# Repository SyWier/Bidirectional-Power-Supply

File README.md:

# Bidirectional-Power-Supply
Development of a bidirectional DC/DC power supply for battery applications.

The designed **developement** board is a **BUCK/BOOST converter**, based on the direction of the power flow. This enables us to charge a battery with voltage reduction or create an uninterrupted voltage output with voltage boost.

The developement board is easily configurable through serial communication, have test points for all the important signals and includes feedback LEDs.

## Directories
- Altium: **Altium** project of the hardware.
- CSS: **Code Composer Studio** project and other tools to flash the microcontroller

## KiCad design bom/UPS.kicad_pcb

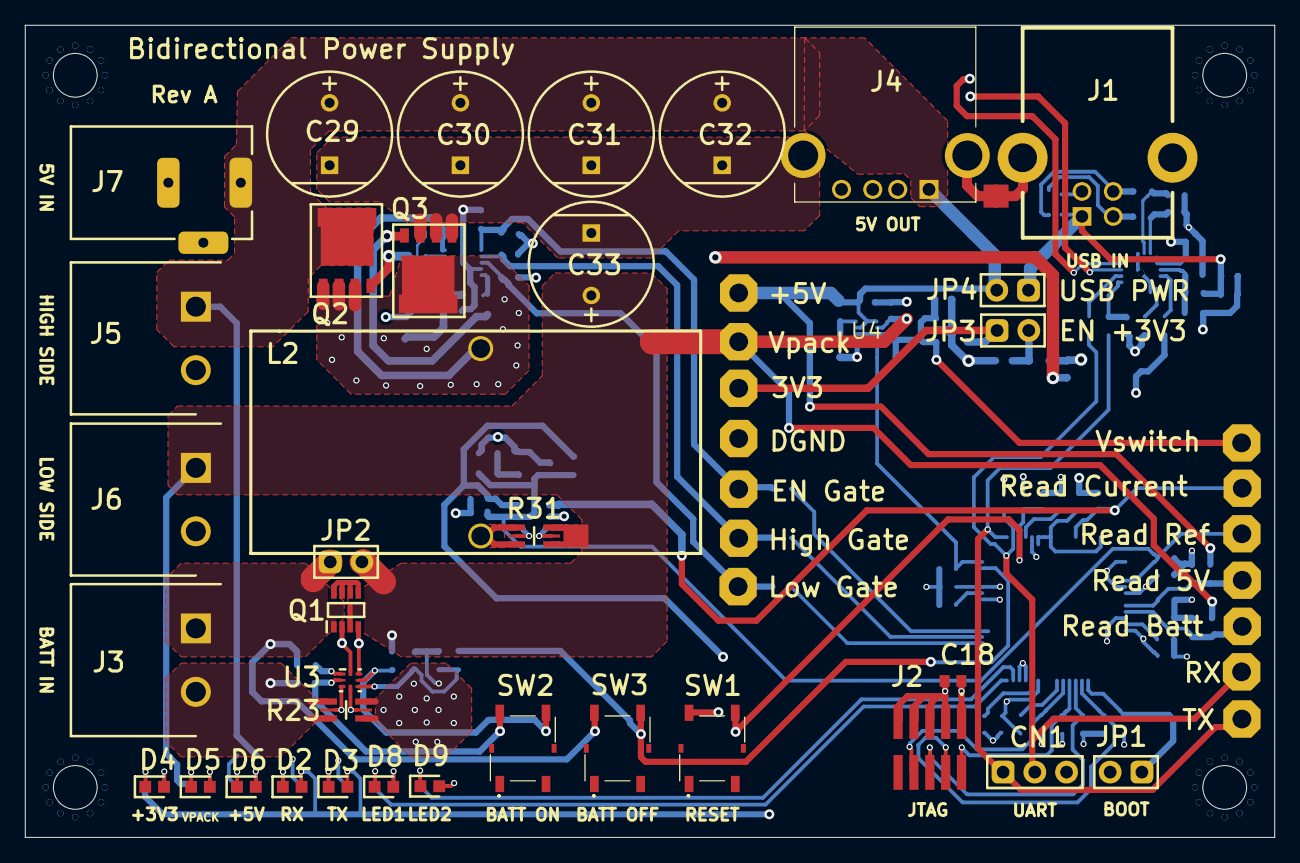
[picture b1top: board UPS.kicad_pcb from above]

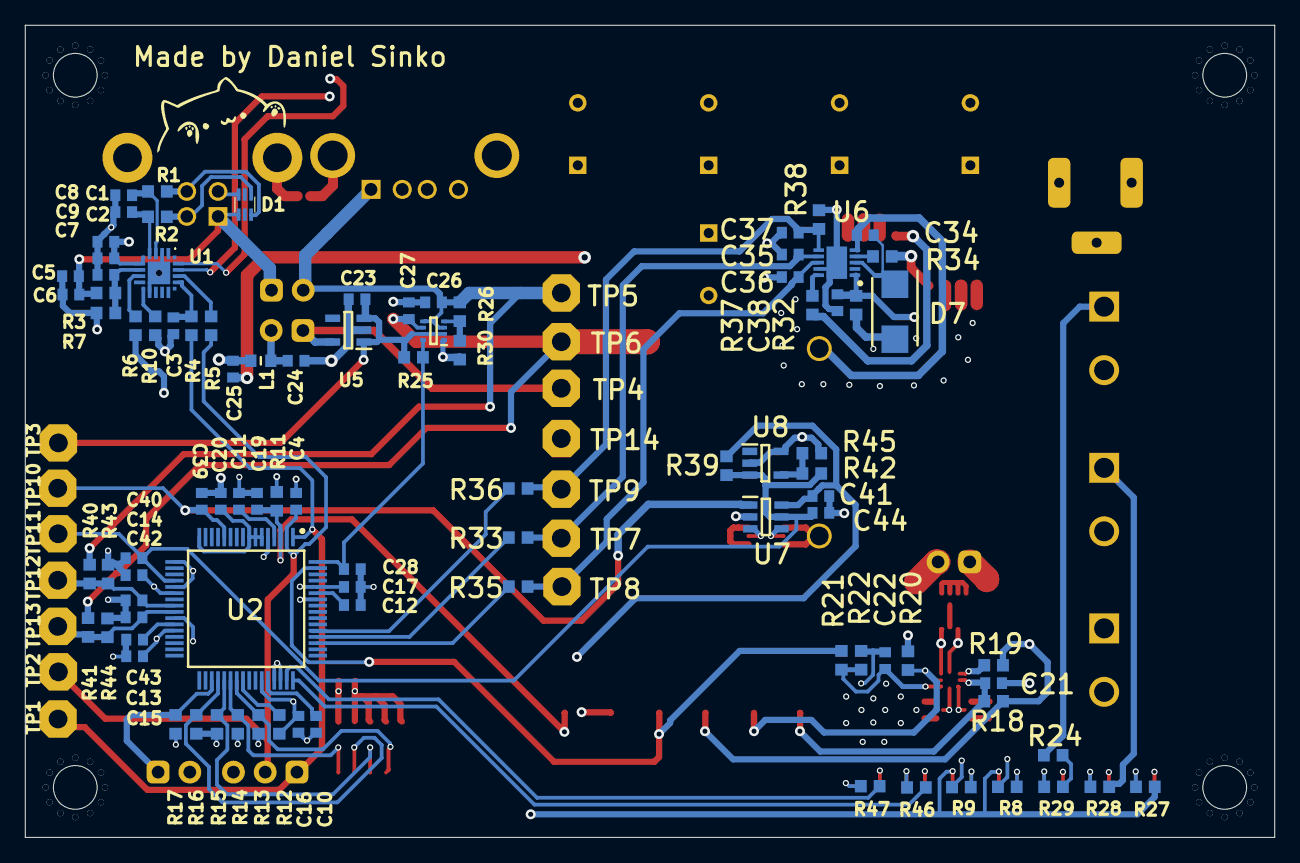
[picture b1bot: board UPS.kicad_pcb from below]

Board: 4 copper layers, 100.0 x 65.0 mm, 149 parts (108 on the bottom side), 78 nets.

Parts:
C1, C2, C35, C36, C37: 47pF; CAP0603
C3, C4: 470pF; CAP0603
C5, C8, C10, C11, C12, C13, C14, C20: 4.7uF; CAP0603
C6, C9, C15, C16, C17, C18, C19, C21, C22, C26, C27, C28, C41, C44: 100nF; CAP0603
C7, C23, C24, C34, C38, C39: 1uF; CAP0603
C25: 10uF; CAP0603
C29, C30, C31, C32: 1500uF; Aluminium Capacitor 10x12.5
C33: 470uF; Aluminium Capacitor 10x12.5
C40, C42, C43: 47nF; CAP0603
CN1: Pins 1x3; PIN-1X3
D1: ESDAULC6-3BP6; SOT-666
D2, D3, D4, D5, D6, D8, D9: Value; LED0603
D7: VS-MBRS130L-M3/5BT; SMB
H1, H2, H3, H4: Mounting_Hole_0; MOUNTING_HOLE_M3
J1: USB-B; USB-B-FEMALE
J2: FTSH-105-01-L-DV-K; CON-2x5-1.27
J3, J5, J6: 691313510002; WR-TBL-5.08/2-M
J4: USB-A; USB-A-FEMALE
J7: DC Power Jack; DC Power Jack Right Angled
JP1, JP2, JP3, JP4: Jumper; PIN-1X2
L1: Inductor; IND0603
L2: Inductor; COIL_HANDMADE
NT1, NT2, NT3: NetTie_1-1; NETTIE_1.85MM
Q1: ECH8695R-TL-W; SOT-28FL
Q2, Q3: N-MOSFET; SOT-669-5
R1, R2, R19: 20R; RES0603
R3: 22K1; RES0603
R4, R5, R18, R21, R33, R35, R36, R39: 100R; RES0603
R6, R20, R22: 1K; RES0603
R7: 47K5; RES0603
R8, R9, R24, R27, R28, R29, R46, R47: 330R; RES0603
R10, R25, R26, R30, R38, R45: 10K; RES0603
R11, R40, R41, R42: 3K3; RES0603
R12, R13, R14, R15, R16, R17, R43, R44: 4K7; RES0603
R23: 0R005; RES1206_KELVIN
R31: 0R010; RES1206_KELVIN
R32, R34, R37: 5R; RES0603
SW1, SW2, SW3: PTS526 Button; PTS526 SMG15J SMTR2 LFS
TP1, TP2, TP3, TP4, TP5, TP6, TP7, TP8, TP9, TP10, TP11, TP12, TP13, TP14: Test Point; TP-1.5HOLE
U1: CP2102N-A02-GQFN20R; QFN-20
U2: F280038PMRQ1; LQFP-64
U3: BQ2980; X2QFN-8
U4: TPS2116; SOTFL50P160X60-8N
U5: LP5907QMFX-3.3Q1; SOT23-5
U6: DGD05473FN-7; V-DFN3030-10
U7: INA181A1; SOT23-6
U8: TLV431; SOT23-5

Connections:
+1V2: C10.2, C11.2, C12.2, C13.2, U2.4, U2.27, U2.44, U2.59
+3V3: C8.2, C9.1, C15.2, C16.2, C17.2, C18.2, C24.2, C41.1, D2.2, D3.2, J2.1, JP3.2, L1.1, R6.1, R11.2, R12.2, R13.2, R14.2, R15.2, R16.2, R17.2, R27.2, R39.1, U1.6, U1.7, U2.28, U2.43, U2.60, U7.6
+3V3A: C14.2, C25.2, L1.2, U2.22
+5V: C26.2, C29.2, C30.2, C31.2, C32.2, C38.2, J4.1, J5.1, J7.1, JP4.2, Q2.3, R24.2, R26.2, R32.1, R40.2, TP5.1, U4.3, U4.5, U6.1
AGND: C14.1, C20.1, C25.1, C39.1, C40.1, C41.2, C42.1, C43.1, C44.2, NT2.2, R43.1, R44.1, R45.1, U2.17, U2.21, U7.2, U8.2, U8.5
BOOT0: R12.1, U2.40
BOOT1: JP1.1, R17.1, U2.35
D+: C1.2, R1.1, U1.4
D-: C2.2, R2.1, U1.5
DGND: C1.1, C2.1, C3.1, C4.1, C5.1, C6.2, C7.1, C8.1, C9.2, C10.1, C11.1, C12.1, C13.1, C15.1, C16.1, C17.1, C18.1, C19.2, C23.1, C24.1, C26.1, C27.1, C28.1, CN1.3, D1.6, D4.1, D8.1, D9.1, J1.0, J1.4, J2.3, J2.5, J2.7, J2.9, JP1.2, NT1.2, NT2.1, R7.1, R10.1, R30.1, SW1.1, TP14.1, U1.3, U1.12, U1.21, U2.5, U2.26, U2.45, U2.46, U2.58, U4.1, U5.2
Gate EN: R36.1, U2.53
Gate High: R33.1, U2.52
Gate Low: R35.1, U2.51
Gate_Common: C34.1, L2.1, Q2.2, Q3.3, U6.5
Gate_High: Q2.1, R34.2
Gate_Low: Q3.1, R37.2
NetC3_2: C3.2, R4.1, U1.17
NetC21_2: C21.2, R18.1, SW2.1, U3.2
NetC22_2: C22.2, R21.1, R22.2, U3.5
NetC34_2: C34.2, D7.1, U6.3
NetC35_2: C35.2, R33.2, TP7.1, U6.7
NetC36_2: C36.2, R35.2, TP8.1, U6.8
NetC37_2: C37.2, R36.2, R38.1, TP9.1, U6.6
NetD1_3: D1.3, J1.3, R1.2
NetD1_4: D1.4, J1.2, R2.2
NetD2_1: D2.1, R8.2
NetD3_1: D3.1, R9.2
NetD4_2: D4.2, R27.1
NetD5_2: D5.2, R28.1
NetD6_2: D6.2, R29.1
NetD7_2: D7.2, R32.2
NetD8_2: D8.2, R46.1
NetD9_2: D9.2, R47.1
NetJP3_1: JP3.1, TP4.1, U5.5
NetL2_2: L2.2, R31.1
NetNT3_1: NT3.1, R31.2
NetQ1_2: Q1.2, U3.8
NetQ1_4: Q1.4, U3.7
NetQ1_5: Q1.5, Q1.6, Q1.7, Q1.8
NetR5_1: R5.1, U1.18
NetR6_2: R6.2, U1.9
NetR8_1: R8.1, U1.20
NetR9_1: R9.1, U1.19
NetR10_2: R10.2, U1.11
NetR19_1: R19.1, U3.1
NetR20_1: R20.1, SW2.2, U3.6
NetR23_3: R23.3, U3.3
NetR23_4: R23.4, U3.4
NetR24_1: R24.1, R29.2
NetR26_1: R26.1, R30.2, U4.4
NetR34_1: R34.1, U6.4
NetR37_1: R37.1, U6.10
NetR42_1: R42.1, R45.2, U8.4
NetR46_2: R46.2, U2.48
NetR47_2: R47.2, U2.47
PGND: C22.1, C29.1, C30.1, C31.1, C32.1, C33.1, C35.1, C36.1, C37.1, C38.1, D5.1, D6.1, J4.4, J4.5, J5.2, J6.2, J7.2, J7.3, NT1.1, Q3.2, R22.1, R23.2, R38.2, U6.9, U6.11
Path Status: C28.2, R25.2, U2.64, U4.8
Read 5V: C42.2, R40.1, R43.2, TP12.1, U2.24
Read Battery: C43.2, R41.1, R44.2, TP13.1, U2.25
Read Current: C39.2, TP10.1, U2.12, U7.1
Read Ref: C40.2, C44.1, R39.2, R42.2, TP11.1, U2.20, U7.5, U8.3
SERIAL_RX: C4.2, CN1.2, R5.2, TP2.1, U2.2
SERIAL_TX: CN1.1, R4.2, TP1.1, U2.1
System Reset: R21.2, SW3.2, U2.63
TCK: J2.4, R16.1, U2.36
TDI: J2.8, R13.1, U2.39
TDO: J2.6, R15.1, U2.37
TMS: J2.2, R14.1, U2.38
VREFHI: C20.2, U2.6, U2.7, U2.8, U2.16
Vbatt+: J3.1, JP2.1, Q1.1, R18.2, R19.2, SW3.1
Vbatt-: C21.1, J3.2, R23.1
Vbus: C7.2, R3.1, R7.2, U1.8
Vim: R31.3, U7.4
Vip: R31.4, U7.3
Vpack: C27.2, C33.2, J6.1, JP2.2, NT3.2, Q1.3, R20.2, R28.2, R41.2, TP6.1, U4.6
Vswitch: C23.2, R25.1, TP3.1, U4.2, U4.7, U5.1, U5.3
Vusb: C5.2, C6.1, D1.1, J1.1, JP4.1, R3.2
XRSN: C19.1, R11.1, SW1.2, U2.3

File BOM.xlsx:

Comment | Description | Designator | Footprint | LibRef | Quantity | Supplier | Supplier Part Number
47pF | Ceramic Capacitor, Multilayer, Ceramic, 100V, 5% +Tol, 5% -Tol, C0G, 30ppm/Cel 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 | C1, C2, C35, C36, C37 | CAP0603 | 47pF | 5 | Mouser | 80-C0603C470J1G
470pF | Ceramic Capacitor, Multilayer, Ceramic, 250V, 5% +Tol, 5% -Tol, C0G, 30ppm/Cel 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 | C3, C4 | CAP0603 | 470pF | 2 | Mouser | 80-C0603C471JAGAUTO
4.7uF | Capacitor Ceramic 4.7uF 10V X5R 10% 0603 T/R | C5, C8, C10, C11, C12, C13, C14, C20 | CAP0603 | 4.7uF | 8 | Mouser | 187-CL10A475KP8NNWC
100nF | Ceramic Capacitor, Multilayer, Ceramic, 25V, 10% +Tol, 10% -Tol, X7R, 15% TC, 0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 | C6, C9, C15, C16, C17, C18, C19, C21, C22, C26, C27, C28, C41, C44 | CAP0603 | 100nF | 14 | Mouser | 187-CL10B104KA8WPNC
1uF | Ceramic Capacitor, Multilayer, Ceramic, 16V, 10% +Tol, 10% -Tol, X7R, 15% TC, 1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 | C7, C23, C24, C34, C38, C39 | CAP0603 | 1uF | 6 | Mouser | 791-SH18B105K160CT
10uF | Ceramic Capacitor, Multilayer, Ceramic, 6.3V, 20% +Tol, 20% -Tol, X5R, 15% TC, 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 | C25 | CAP0603 | 10uF | 1 | Mouser | 187-CL10A106MQ8NNND
1500uF | Aluminum Electrolytic Capacitor, Polarized, Aluminum (solid Polymer), 6.3V, 20%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 | C29, C30, C31, C32 | Aluminium Capacitor 10x12.5 | 1500uF | 4 | Mouser | 647-RNU0J152MDN1PH
470uF | Aluminum Electrolytic Capacitor, Aluminum (solid Polymer) | C33 | Aluminium Capacitor 10x12.5 | RR50J471MDN1KX | 1 | Mouser | 647-RR50J471MDN1KX
47nF | Ceramic Capacitor, Multilayer, Ceramic, 16V, 10% +Tol, 10% -Tol, X7R, 15% TC, 0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 | C40, C42, C43 | CAP0603 | 47nF | 3 | Mouser | 77-VJ0603Y473KXJCBC
Pins 1x3 | 1x3 2.54mm | CN1 | PIN-1X3 | Pins 1x3 | 1
ESDAULC6-3BP6 | Trans Voltage Suppressor Diode, Bidirectional, 4 Element, Silicon | D1 | SOT-666 | ESDAULC6-3BP6 | 1 | Mouser | 511-ESDAULC63BP6
Value | Single Color LED, Bright Green, Water Clear, 1.1mm | D2, D3, D4, D5, D6, D8, D9 | LED0603 | LED Green | 7 | Mouser | 710-150060VS75000
VS-MBRS130L-M3/5BT | Rectifier Diode, Schottky, 1 Phase, 1 Element, 30V V(RRM), Silicon | D7 | SMB | VS-MBRS130L-M3/5BT | 1 | Mouser | 78-VS-MBRS130L-M35BT
Mounting_Hole_0 | Mounting hole with no connectivity. | H1, H2, H3, H4 | MOUNTING_HOLE_M3 | Mounting_Hole_0 | 4
USB-B | USB Connector, 4 Contact(s), Female, Right Angle, Solder Terminal, Receptacle | J1 | USB-B-FEMALE | USB-B | 1 | Mouser | 490-UJ2-BH-W2-TH
FTSH-105-01-L-DV-K | Board Connector, 10 Contact(s), 2 Row(s), Male, Straight, 0.05 inch Pitch, Surf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 | J2 | CON-2x5-1.27 | Connector_10Pin | 1 | Mouser | 200-FTSH10501LDVKP
691313510002 | Wurth Elektronik, 2 Pin Pluggable Terminal Block, Male | J3, J5, J6 | WR-TBL-5.08/2-M | 691313510002 | 3 | Mouser | 710-691313510002
USB-A | USB Connector | J4 | USB-A-FEMALE | USB-A | 1 | Mouser | 530-SS-52100-001
DC Power Jack | CIRCULAR DC POWER CONNECTOR | J7 | DC Power Jack Right Angled | DC Power Jack | 1 | Mouser | 710-694106301002
Jumper | Interconnection Device | JP1, JP2, JP3, JP4 | PIN-1X2 | Jumper | 4 | Mouser | 855-M7582-46
Inductor | General Purpose Inductor, 10uH, 20%, 1 Element, Ferrite-Core, SMD, 1608M | L1 | IND0603 | 10uH | 1 | Mouser | 810-MLZ1608E100MT
Inductor | Hand made inductance | L2 | COIL_HANDMADE | Inductor | 1
691351500002 | Wurth Elektronik, 2 Pin Pluggable Terminal Block, Female | P1, P2, P3 | WR-TBL-5.08/2-F | 691351500002 | 3 | Mouser | 710-691351500002
ECH8695R-TL-W | Power Field-Effect Transistor, 11A I(D), N-Channel, Metal-oxide Semiconductor F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 | Q1 | SOT-28FL | ECH8695R-TL-W | 1 | Mouser | 863-ECH8695R-TL-W
N-MOSFET | Power Field-Effect Transistor, 100A I(D), 25V, 0.00169ohm, 1-Element, N-Channel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 | Q2, Q3 | SOT-669-5 | PSMN1R2-25YLDX | 2 | Mouser | 771-PSMN1R2-25YLDX
20R | Fixed Resistor, Metal Glaze/thick Film, 0.1W, 20ohm, 75V, 1% +/-Tol, 100ppm/Cel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 | R1, R2, R19 | RES0603 | 20R | 3 |  | 71-CRCW0603-20-E3
22K1 | 22.1K F 1/16 0603 | R3 | RES0603 | 22K1 | 1 |  | 791-RMC1/16K2212FTP
100R | Fixed Resistor, Metal Glaze/thick Film, 0.1W, 100ohm, 75V, 5% +/-Tol, 100ppm/Ce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 | R4, R5, R18, R21, R33, R35, R36, R39 | RES0603 | 100R | 8 |  | 603-RC0603JR-13100RL
1K | Fixed Resistor, Metal Glaze/thick Film, 0.1W, 1000ohm, 75V, 1% +/-Tol, 100ppm/C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 | R6, R20, R22 | RES0603 | 1K | 3 |  | 652-CR0603FX-1001ELF
47K5 | Fixed Resistor, Metal Glaze/thick Film, 0.1W, 47500ohm, 75V, 1% +/-Tol, 100ppm/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 | R7 | RES0603 | 47K5 | 1 |  | 603-RC0603FR-0747K5L
330R | Fixed Resistor, Metal Glaze/thick Film, 0.1W, 330ohm, 75V, 1% +/-Tol, 100ppm/Ce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 | R8, R9, R24, R27, R28, R29, R46, R47 | RES0603 | 330R | 8 |  | 791-WR06X3300FTL
10K | Fixed Resistor, Metal Glaze/thick Film, 0.1W, 10000ohm, 75V, 1% +/-Tol, 100ppm/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 | R10, R25, R26, R30, R38, R45 | RES0603 | 10K | 6 |  | 652-CR0603FX-1002ELF
3K3 | Fixed Resistor, Metal Glaze/thick Film, 0.1W, 3300ohm, 75V, 1% +/-Tol, 100ppm/C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 | R11, R40, R41, R42 | RES0603 | 3K3 | 4 | Mouser | 603-RC0603FR-073K3L
4K7 | Fixed Resistor, Metal Glaze/thick Film, 0.1W, 4700ohm, 75V, 1% +/-Tol, 100ppm/C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 | R12, R13, R14, R15, R16, R17, R43, R44 | RES0603 | 4K7 | 8 |  | 603-AC0603FR-134K7L
0R005 | Resistor Current Sense Metal Foil 1206 5m Ohm 1% 1W ±50ppm/°C T/R | R23 | RES1206_KELVIN | 0R005 | 1 |  | 504-MFSA1206R0050FCM
0R010 | Resistor Current Sense Metal Foil 1206 10m Ohm 1% 1W ±50ppm/°C T/R | R31 | RES1206_KELVIN | 0R010 | 1 |  | 504-MFSA1206R0050FCM
5R1 | Fixed Resistor, Thin Film, 0.1W, 5.1ohm, 75V, 0.5% +/-Tol, 25ppm/Cel, Surface M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 | R32, R34, R37 | RES0603 | 5R | 3 |  | 603-RT0603DRD075R1L
PTS526 Button | PTS526 Series SPST-NO Off-Mom 160 gf Top Actuated J Lead SMT Tactile Switch | SW1, SW2, SW3 | PTS526 SMG15J SMTR2 LFS | PTS526 Button | 3 | Mouser | 611-TS526SMG15JSMR2L
Test Point | Test Point | TP1, TP2, TP3, TP4, TP5, TP6, TP7, TP8, TP9, TP10, TP11, TP12, TP13, TP14 | TP-1.5HOLE | Test Point | 14
CP2102N-A02-GQFN20R | USB Bus Controller, CMOS | U1 | QFN-20 | CP2102N-A02-GQFN20R | 1 | Mouser | 634-CP2102NA02QFN20R
F280038PMRQ1 | Automotive C2000™ 32-bit MCU 120-MHz 384-KB flash, FPU, TMU with CLA, AES and C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 | U2 | LQFP-64 | F280038CPMRQ1 | 1 | Mouser | 595-F280038PMRQ1
BQ2980 | High-side protector for single-cell Li-ion and Li-polymer batteries with 0-V ch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 | U3 | X2QFN-8 | BQ2980 | 1 | Mouser | 595-BQ298217RUGR
TPS2116 | Single-Ended Multiplexer, 1 Func, 2 Channel, PDSO8 | U4 | SOTFL50P160X60-8N | TPS2116 | 1 | Mouser | 595-TPS2116DRLR
LP5907QMFX-3.3Q1 | Fixed Positive LDO Regulator, 3.3V, 0.25V Dropout, PDSO5 | U5 | SOT23-5 | LP5907QMFX-3.3Q1 | 1 | Mouser | 595-LP5907QMFX-3.3Q1
DGD05473FN-7 | Half Bridge Based MOSFET Driver | U6 | V-DFN3030-10 | DGD05473FN-7 | 1 | Mouser | 621-DGD05473FN-7
INA181A1 | Operational Amplifier, 1 Func, 500uV Offset-Max, PDSO6 | U7 | SOT23-6 | INA181A1 | 1 | Mouser | 595-INA181A1IDBVR
TLV431 | Three Terminal Voltage Reference, 1 Output, 1.24V, Trim/Adjustable, BIPolar, PD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 | U8 | SOT23-5 | TLV431 | 1 | Mouser | 595-TLV431CDBVR

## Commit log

2024-09-26 Project created
2024-10-14 Added basic circuits
    And some alternatives
2024-10-14 Power Path + LDO
2024-10-15 New gate driver + low side driver
2024-10-16 Sch redesign, measurements
2024-10-17 Created main sheet
2024-10-26 Analog 3v3 and GND
2024-10-30 New gate driver circuit
    Deleted aux driver
2024-10-31 PCB Progress
2024-11-01 Added jumpers, removed battery
    Smaller PCB
2024-11-02 Modified REF voltage and current read
2024-11-02 1206 4-wire kelvin footprints
2024-11-03 Added line capacitors
2024-11-03 Battery protection turn on
2024-11-03 Modified connectors
2024-11-03 Separeted grounds
2024-11-03 Added test points
2024-11-03 Added even more capacitors
2024-11-03 Routed gate driver
2024-11-04 Routed current sensor
2024-11-05 Routed battery protection
2024-11-05 Added mounting holes
2024-11-05 Routed usb-uart bridge
2024-11-05 Routed power path switch
2024-11-05 Routed 3V3 LDO
2024-11-05 uC capacitors
2024-11-05 Routed uC
2024-11-06 Finished most of the routing
    Finished test points
2024-11-06 Routed all leds
2024-11-06 Cleaned up silkscreen
2024-11-06 Cleaned design rule check
2024-11-06 Moved connectors closer to the edge
2024-11-06 Improved AGND routing
2024-11-06 Cleared design rule check
    Also added some thermal vias
2024-11-06 Added silkscreen texts
    And bongo cat :3
2024-12-01 Improved schematic layout
2024-12-01 Added datasheets
2024-12-01 Refactor file structure
2024-12-01 Moved README.md
2024-12-06 Added files to folders and documentation
2024-12-06 Fájlok nevének megváltoztatása
2024-12-06 Hivatkozás és pdf frissítése
2025-06-02 Moved hw files
2025-06-02 Added Altium README.md
2025-06-02 Deleted old hw files
2025-06-02 Added .gitignore file
2025-06-02 Deleted files
2025-06-02 Added README.md
2025-11-11 Updated code base from local project
